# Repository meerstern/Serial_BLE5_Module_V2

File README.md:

# BLE5モジュール変換基板V2 
Serial_BLE5_Module_V2 is Lyra P module board with Wireless Xpress Firm.  

## 概要 
  * Laird Connectivity社製のBLEモジュール、Lyra Pを搭載した変換基板です  
  * Silicon Labs社のBGXシリーズで採用されていたWireless Xpress互換ファームを出荷時に書き込んでいます  
  * Wireless Xpress互換ファームで簡易なUARTコマンドを用いてBluetooh通信を使用できます  
  * スマートフォンや他のWireless Xpressモジュールと容易に接続することが可能です  
  * [Wireless Xpressファームの他、AT Command Setファーム][7]や開発環境によるカスタムファームを利用できます  
  * ファームの書き換えはUSBシリアルUART変換アダプタ(CTS,RTS接続必須)等を介して書き換えできます  
  * 電源電圧範囲1.8V~3.8V  
  * 3.3Vシリアル通信(UART,初期115200bps)で外部機器からパラメータを設定できます  
  * 3.3Vシリアル通信はGROVEコネクタ互換でも接続できます  
  * BGX13Pを使用した[BLE5モジュール変換基板][6]と同じピンアサインとサイズです  
  * TELEC(技適)認証済 工事設計認証番号 [209-J00456][5]  
  * 基板サイズ25mm x25mm(Grove互換コネクタ突起部除く)  

## 販売サイト
  * [スイッチサイエンス][8]

## 関連情報
 * [データシート][1]
 * [Laird Connectivity社 Lyra P製品サイト][2]
 * Wireless Xpressマクニカ製品紹介サイト[その１][3]、[その２][4]  

[1]: https://www.lairdconnect.com/documentation/datasheet-lyra-p
[2]: https://www.lairdconnect.com/wireless-modules/bluetooth-modules/bluetooth-5-modules/lyra-series-bluetooth-53-modules

[3]: https://service.macnica.co.jp/library/130293
[4]: https://service.macnica.co.jp/library/130269
[5]: https://www.tele.soumu.go.jp/giteki/SearchServlet?pageID=jg01_01&PC=209&TC=N&PK=1&FN=220428N209&SN=%94%46%8F%D8&LN=3&R1=*****&R2=*****
[6]: https://github.com/meerstern/Serial_BLE5_Module
[7]: https://github.com/LairdCP/Lyra_Firmware
[8]: https://www.switch-science.com/products/8649

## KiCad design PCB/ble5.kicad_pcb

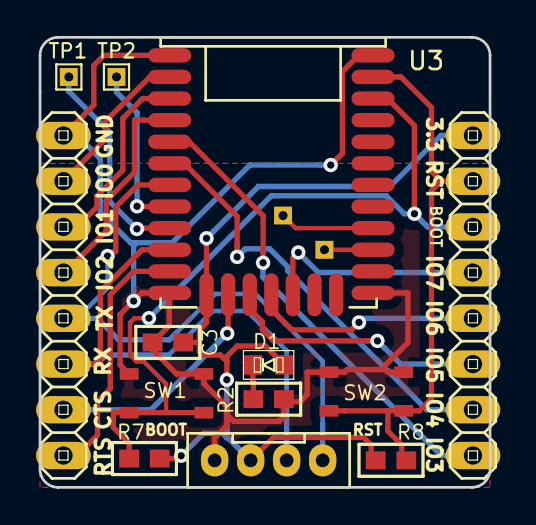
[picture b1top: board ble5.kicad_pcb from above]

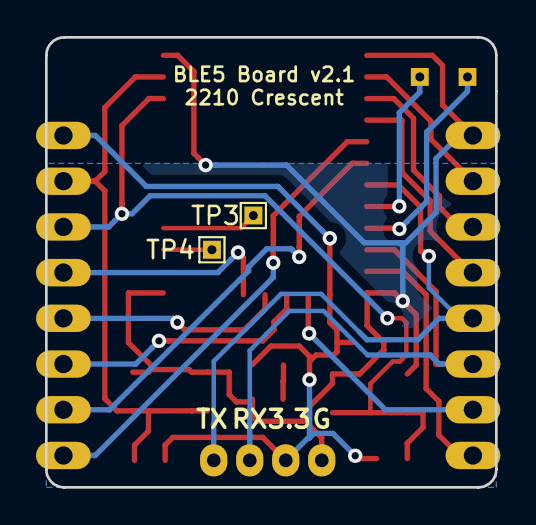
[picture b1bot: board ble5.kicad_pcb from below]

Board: 2 copper layers, 25.0 x 25.0 mm, 15 parts (2 on the bottom side), 21 nets.

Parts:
C3: 0.1u; C-0603
D1: LED; generic-LED1608
P1, P2: CONN_01X08; pinhead-1X08
P3: CONN_01X04; GROVE
R2: 1k; R-0603
R7, R8: 20k; R-0603
SW1, SW2: SW_Push; SKRPACE010
TP1: SWDIO; TestPoint_THTPad_1.0x1.0mm_Drill0.5mm
TP2: SWCLK; TestPoint_THTPad_1.0x1.0mm_Drill0.5mm
TP3: PTI_DATA; TestPoint_THTPad_1.0x1.0mm_Drill0.5mm
TP4: PTI_FRAME; TestPoint_THTPad_1.0x1.0mm_Drill0.5mm
U3: LyraP; bgm13p-smd

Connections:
+3V3: C3.1, D1.A, P2.8, P3.3, R7.1, R8.1, U3.13
/BLE_RX: P1.6, P3.2, U3.10
/BLE_TX: P1.5, P3.1, U3.7
/BOOT: P2.6, R7.2, SW1.1, U3.29
/CTS: P1.7, U3.14
/GPIO0: P1.2, U3.2
/GPIO1: P1.3, U3.3
/GPIO2: P1.4, U3.4
/GPIO3: P2.1, U3.5
/GPIO4: P2.2, U3.6
/GPIO5: P2.3, U3.15
/GPIO6: P2.4, U3.16
/GPIO7: P2.5, U3.17
/RST: P2.7, R8.2, SW2.1, U3.30
/RTS: P1.8, U3.11
GND: C3.2, P1.1, P3.4, R2.2, SW1.2, SW2.2, U3.1, U3.12, U3.20, U3.31
unnamed: D1.K, R2.1
unnamed: TP1.1, U3.9
unnamed: TP2.1, U3.8
unnamed: TP3.1, U3.23
unnamed: TP4.1, U3.22

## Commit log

2022-10-24 Add images
2022-10-24 Add PCB Data
